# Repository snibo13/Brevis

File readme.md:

An 8 key macro pad with a rotary encoder and built-in-switch. Running on a Pro Micro.

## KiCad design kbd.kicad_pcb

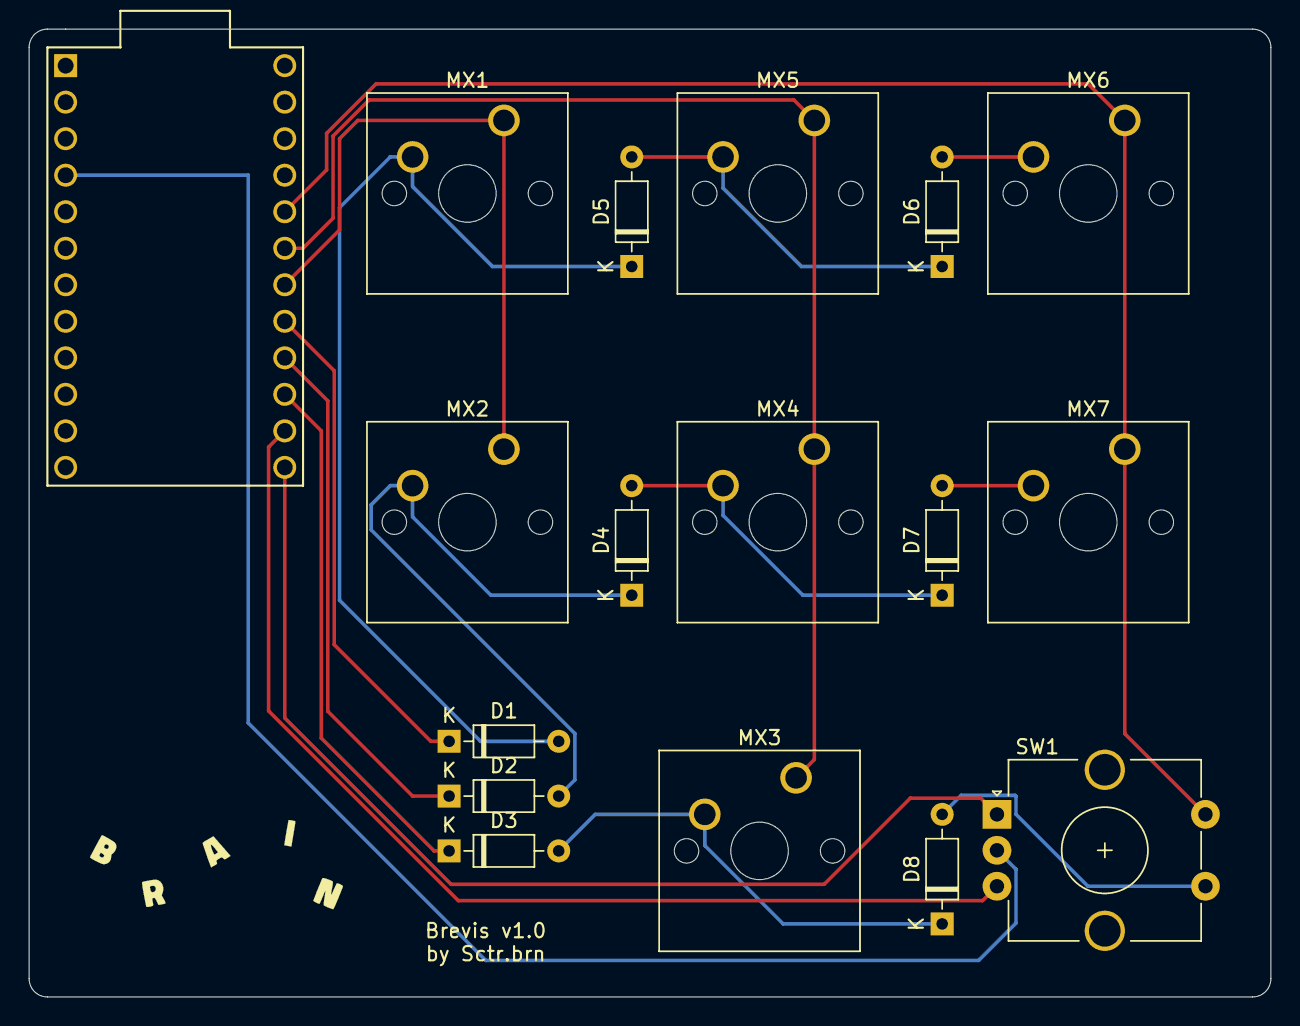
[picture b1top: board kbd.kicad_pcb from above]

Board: 2 copper layers, 86.4 x 67.3 mm, 17 parts (0 on the bottom side), 17 nets.

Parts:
D1, D2, D3, D4, D5, D6, D7, D8: 1N4148; D_DO-35_SOD27_P7.62mm_Horizontal
MX1, MX2, MX3, MX4, MX5, MX6, MX7: MX-NoLED; SW_Cherry_MX_1.00u_PCB
SW1: Rotary_Encoder_Switch; RotaryEncoder_Alps_EC12E-Switch_Vertical_H20mm_CircularMoun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
U1: ProMicro

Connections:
Col1: MX1.1, MX2.1, U1.18
Col2: MX3.1, MX4.1, MX5.1, U1.19
Col3: MX6.1, MX7.1, SW1.S1, U1.20
ENCA: SW1.A, U1.13
ENCB: SW1.B, U1.14
unnamed: D1.2, D5.1, MX1.2
unnamed: D2.2, D4.1, MX2.2
unnamed: D3.2, D8.1, MX3.2
unnamed: D4.2, D7.1, MX4.2
unnamed: D5.2, D6.1, MX5.2
unnamed: D6.2, MX6.2
unnamed: D7.2, MX7.2
unnamed: D8.2, SW1.S2
unnamed: SW1.C, U1.4
Row1: D1.1, U1.17
Row2: D2.1, U1.16
Row3: D3.1, U1.15

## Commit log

2021-01-19 Version 1.0
2021-01-19 Adding Readme
